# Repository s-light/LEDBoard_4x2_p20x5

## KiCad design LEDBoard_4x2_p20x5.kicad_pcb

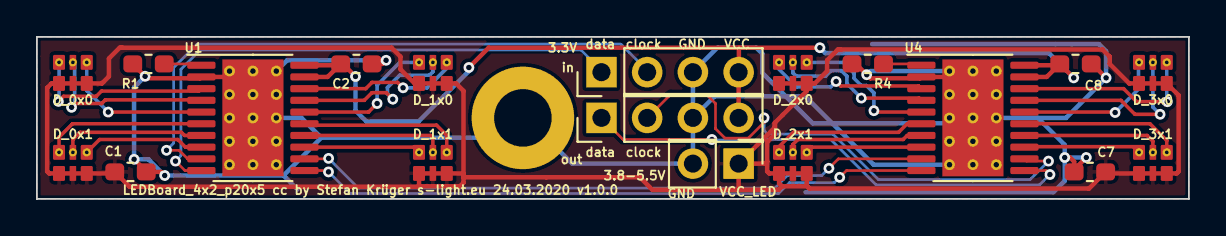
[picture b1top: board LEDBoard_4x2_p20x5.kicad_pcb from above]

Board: 2 copper layers, 64.0 x 9.0 mm, 20 parts (0 on the bottom side), 35 nets.

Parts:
C1, C7: 10uF 6.3V; C_0603_1608Metric_Pad1.05x0.95mm_HandSolder
C2, C8: 100n; C_0603_1608Metric_Pad1.05x0.95mm_HandSolder
D_0x0, D_0x1, D_1x0, D_1x1, D_2x0, D_2x1, D_3x0, D_3x1: LED_RGB; LED_RGB_0706_1816Metric_ROHM_ThermalVias
H1: MH_M3; MountingHole_3.2mm_M3_ISO7380_Pad
J1: signal_in; PinHeader_1x04_P2.54mm_Vertical
J2: signal_out; PinHeader_1x04_P2.54mm_Vertical
J3: power; PinHeader_1x02_P2.54mm_Vertical
R1, R4: 2k7 0.1%; R_0603_1608Metric_Pad1.05x0.95mm_HandSolder
U1, U4: TLC5971PWP; HTSSOP-20-1EP_4.4x6.5mm_P0.65mm_EP3.4x6.5mm_Mask2.75x3.43mm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

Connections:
/clock_1-2: U1.12, U4.9
/clock_in: J1.2, U1.9
/clock_out: J2.2, U4.12
/data_1-2: U1.11, U4.10
/data_in: J1.1, U1.10
/data_out: J2.1, U4.11
/led_0x0_b: D_0x0.3, U1.5
/led_0x0_g: D_0x0.2, U1.4
/led_0x0_r: D_0x0.1, U1.3
/led_0x1_b: D_0x1.3, U1.8
/led_0x1_g: D_0x1.2, U1.7
/led_0x1_r: D_0x1.1, U1.6
/led_1x0_b: D_1x0.3, U1.18
/led_1x0_g: D_1x0.2, U1.17
/led_1x0_r: D_1x0.1, U1.16
/led_1x1_b: D_1x1.3, U1.15
/led_1x1_g: D_1x1.2, U1.14
/led_1x1_r: D_1x1.1, U1.13
/led_2x0_b: D_2x0.3, U4.5
/led_2x0_g: D_2x0.2, U4.4
/led_2x0_r: D_2x0.1, U4.3
/led_2x1_b: D_2x1.3, U4.8
/led_2x1_g: D_2x1.2, U4.7
/led_2x1_r: D_2x1.1, U4.6
/led_3x0_b: D_3x0.3, U4.18
/led_3x0_g: D_3x0.2, U4.17
/led_3x0_r: D_3x0.1, U4.16
/led_3x1_b: D_3x1.3, U4.15
/led_3x1_g: D_3x1.2, U4.14
/led_3x1_r: D_3x1.1, U4.13
GND: C1.2, C2.2, C7.2, C8.2, H1.1, J1.3, J2.3, J3.2, R1.2, R4.2, U1.2, U1.21, U4.2, U4.21
unnamed: R1.1, U1.1
unnamed: R4.1, U4.1
VCC: C2.1, C8.1, J1.4, J2.4, U1.19, U1.20, U4.19, U4.20
VCC_LED: C1.1, C7.1, D_0x0.4, D_0x0.5, D_0x0.6, D_0x1.4, D_0x1.5, D_0x1.6, D_1x0.4, D_1x0.5, D_1x0.6, D_1x1.4, D_1x1.5, D_1x1.6, D_2x0.4, D_2x0.5, D_2x0.6, D_2x1.4, D_2x1.5, D_2x1.6, D_3x0.4, D_3x0.5, D_3x0.6, D_3x1.4, D_3x1.5, D_3x1.6, J3.1

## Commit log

2020-03-24 import LEDBoard_4x2_p20x5
2020-03-24 export gerber
2020-03-24 update readme and exports
2020-03-25 export: added Excellon drill files

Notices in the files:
LEDBoard_4x2_p20x5.kicad_pcb:
cc by Stefan Krüger s-light.eu
LEDBoard_4x2_p20x5 cc by Stefan Krüger s-light.eu 24.03.2020 v1.0.0
